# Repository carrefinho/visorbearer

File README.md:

# Visorbearer

Visorbearer is a 32-key unibody split wireless keyboard featuring 8 RGB LED indicators.

Named after [hummingbirds in the genus Augastes](https://en.wikipedia.org/wiki/Visorbearer) for the Hummingbird layout connection and distinctive white bands on their chests that resemble the LED indicators.

> [!WARNING]
> This is a work in progress.

## To-Do

- [ ] Build Guide & BOM
- [ ] Case Printing Guide
- [ ] Alternative layout case files and guide
- [x] Revision 2 PCB testing + power profiling
- [x] Firmware Notes
- [ ] Design write-up
- [ ] More photos

## Design

https://github.com/user-attachments/assets/812049e3-29ce-48d4-8fe3-20bf21285e64

- 2x 4-segment RGB LED indicators
   - Discreet dead-front design: completely invisible when off
   - Connection bar: Bluetooth profiles and modifier keys
   - Battery bar: percentage and charging status
   - Powered by two TI LP5012 drivers with automatic low-power mode
- 32-key Hummingbird-ish layout with splay and inverted thumb cluster
   - Down to 26-key with case and plate variants
      - 2U thumb key support
- Hot-swap Kailh Choc v1 switches in Choc (18x17mm) spacing
   - <details> <summary>Limited Choc v2 compatibility</summary>

      The PCB is incompatible with older Choc v2 switches that have a third stabilizing pin. Newer Choc v2 releases without this pin work fine, such as: Lofree POM Phantom/Ghost/Specter/Hades and Kailh Hide Mountain/White Rain/Deep Sea Mini Islet/Deep Sea Mini Whale.

      Note that, for Choc v2, there are very few off-the-shelf options for choc-spaced keycaps with MX stems: as of late 2025, the only two are [Taihao THCS](https://shop.tai-hao.com/categories/thcs-low-profile-keycaps) and [Asymplex MX-stem Chicago Steno](https://www.asymplex.xyz/product/made-to-order-mx-stem-cs-kits). You could also 3D-print your own keycaps.

   </details>
- Seeed Studio XIAO nRF52840 **Plus** controller on ZMK firmware
- 3D-printed case and switch plate with switch puller grooves
   - Easily accessible reset button

<picture>
  <source media="(prefers-color-scheme: dark)" srcset="./docs/images/visorbearer-dimensions-dark.png">
  <source media="(prefers-color-scheme: light)" srcset="./docs/images/visorbearer-dimensions-light.png">
  
</picture>

## Build Guide

> [!NOTE]
> Revision 2 PCB is tested and working. Build guide is work in progress.

[View the PCB on KiCanvas.](https://kicanvas.org/?github=https%3A%2F%2Fgithub.com%2Fcarrefinho%2Fvisorbearer%2Ftree%2Fmain%2Fvisorbearer-pcb)

[Find the build guide here.](/docs/build-guide.md)

## Firmware

[Find the ZMK module here.](https://github.com/carrefinho/visorbearer-zmk-module)

## Gallery

## Inspirations & Acknowledgments

- Aesthetics
   - [GEIGEIGEIST/TOTEM](https://github.com/GEIGEIGEIST/TOTEM)
   - [weteor/Grumpy](https://github.com/weteor/Grumpy)
   - [dohn-joh/alias](https://github.com/dohn-joh/alias)
- Layout
   - [bennytrouser/NostrumX](https://github.com/bennytrouser/NostrumX)
   - [davidphilipbarr/hypergolic](https://github.com/davidphilipbarr/hypergolic)
   - [davidphilipbarr/paroxysm](https://github.com/davidphilipbarr/paroxysm)
   - [grassfedreeve/akohekohe](https://github.com/grassfedreeve/akohekohe)
   - [hazels-garage/bad-wings](https://github.com/hazels-garage/bad-wings/tree/master/v2)
   - [kilipan/zilpzalp](https://github.com/kilipan/zilpzalp)
   - [weteor/Fitis](https://github.com/weteor/Fitis)
   - [weteor/Tipper-TF](https://github.com/weteor/Tipper-TF)
- LED indicator
   - [GEIGEIGEIST/KLOTZ](https://github.com/GEIGEIGEIST/KLOTZ)
   - [caksoylar/zmk-rgbled-widget](https://github.com/caksoylar/zmk-rgbled-widget): LED code
- Case
   - [duckyb/urchin](https://github.com/duckyb/urchin): Snap fit design
- And the lovely folks on the Fingerpunch discord who were along for the ride!

## License

Visorbearer is licensed under CERN-OHL-P-2.0.

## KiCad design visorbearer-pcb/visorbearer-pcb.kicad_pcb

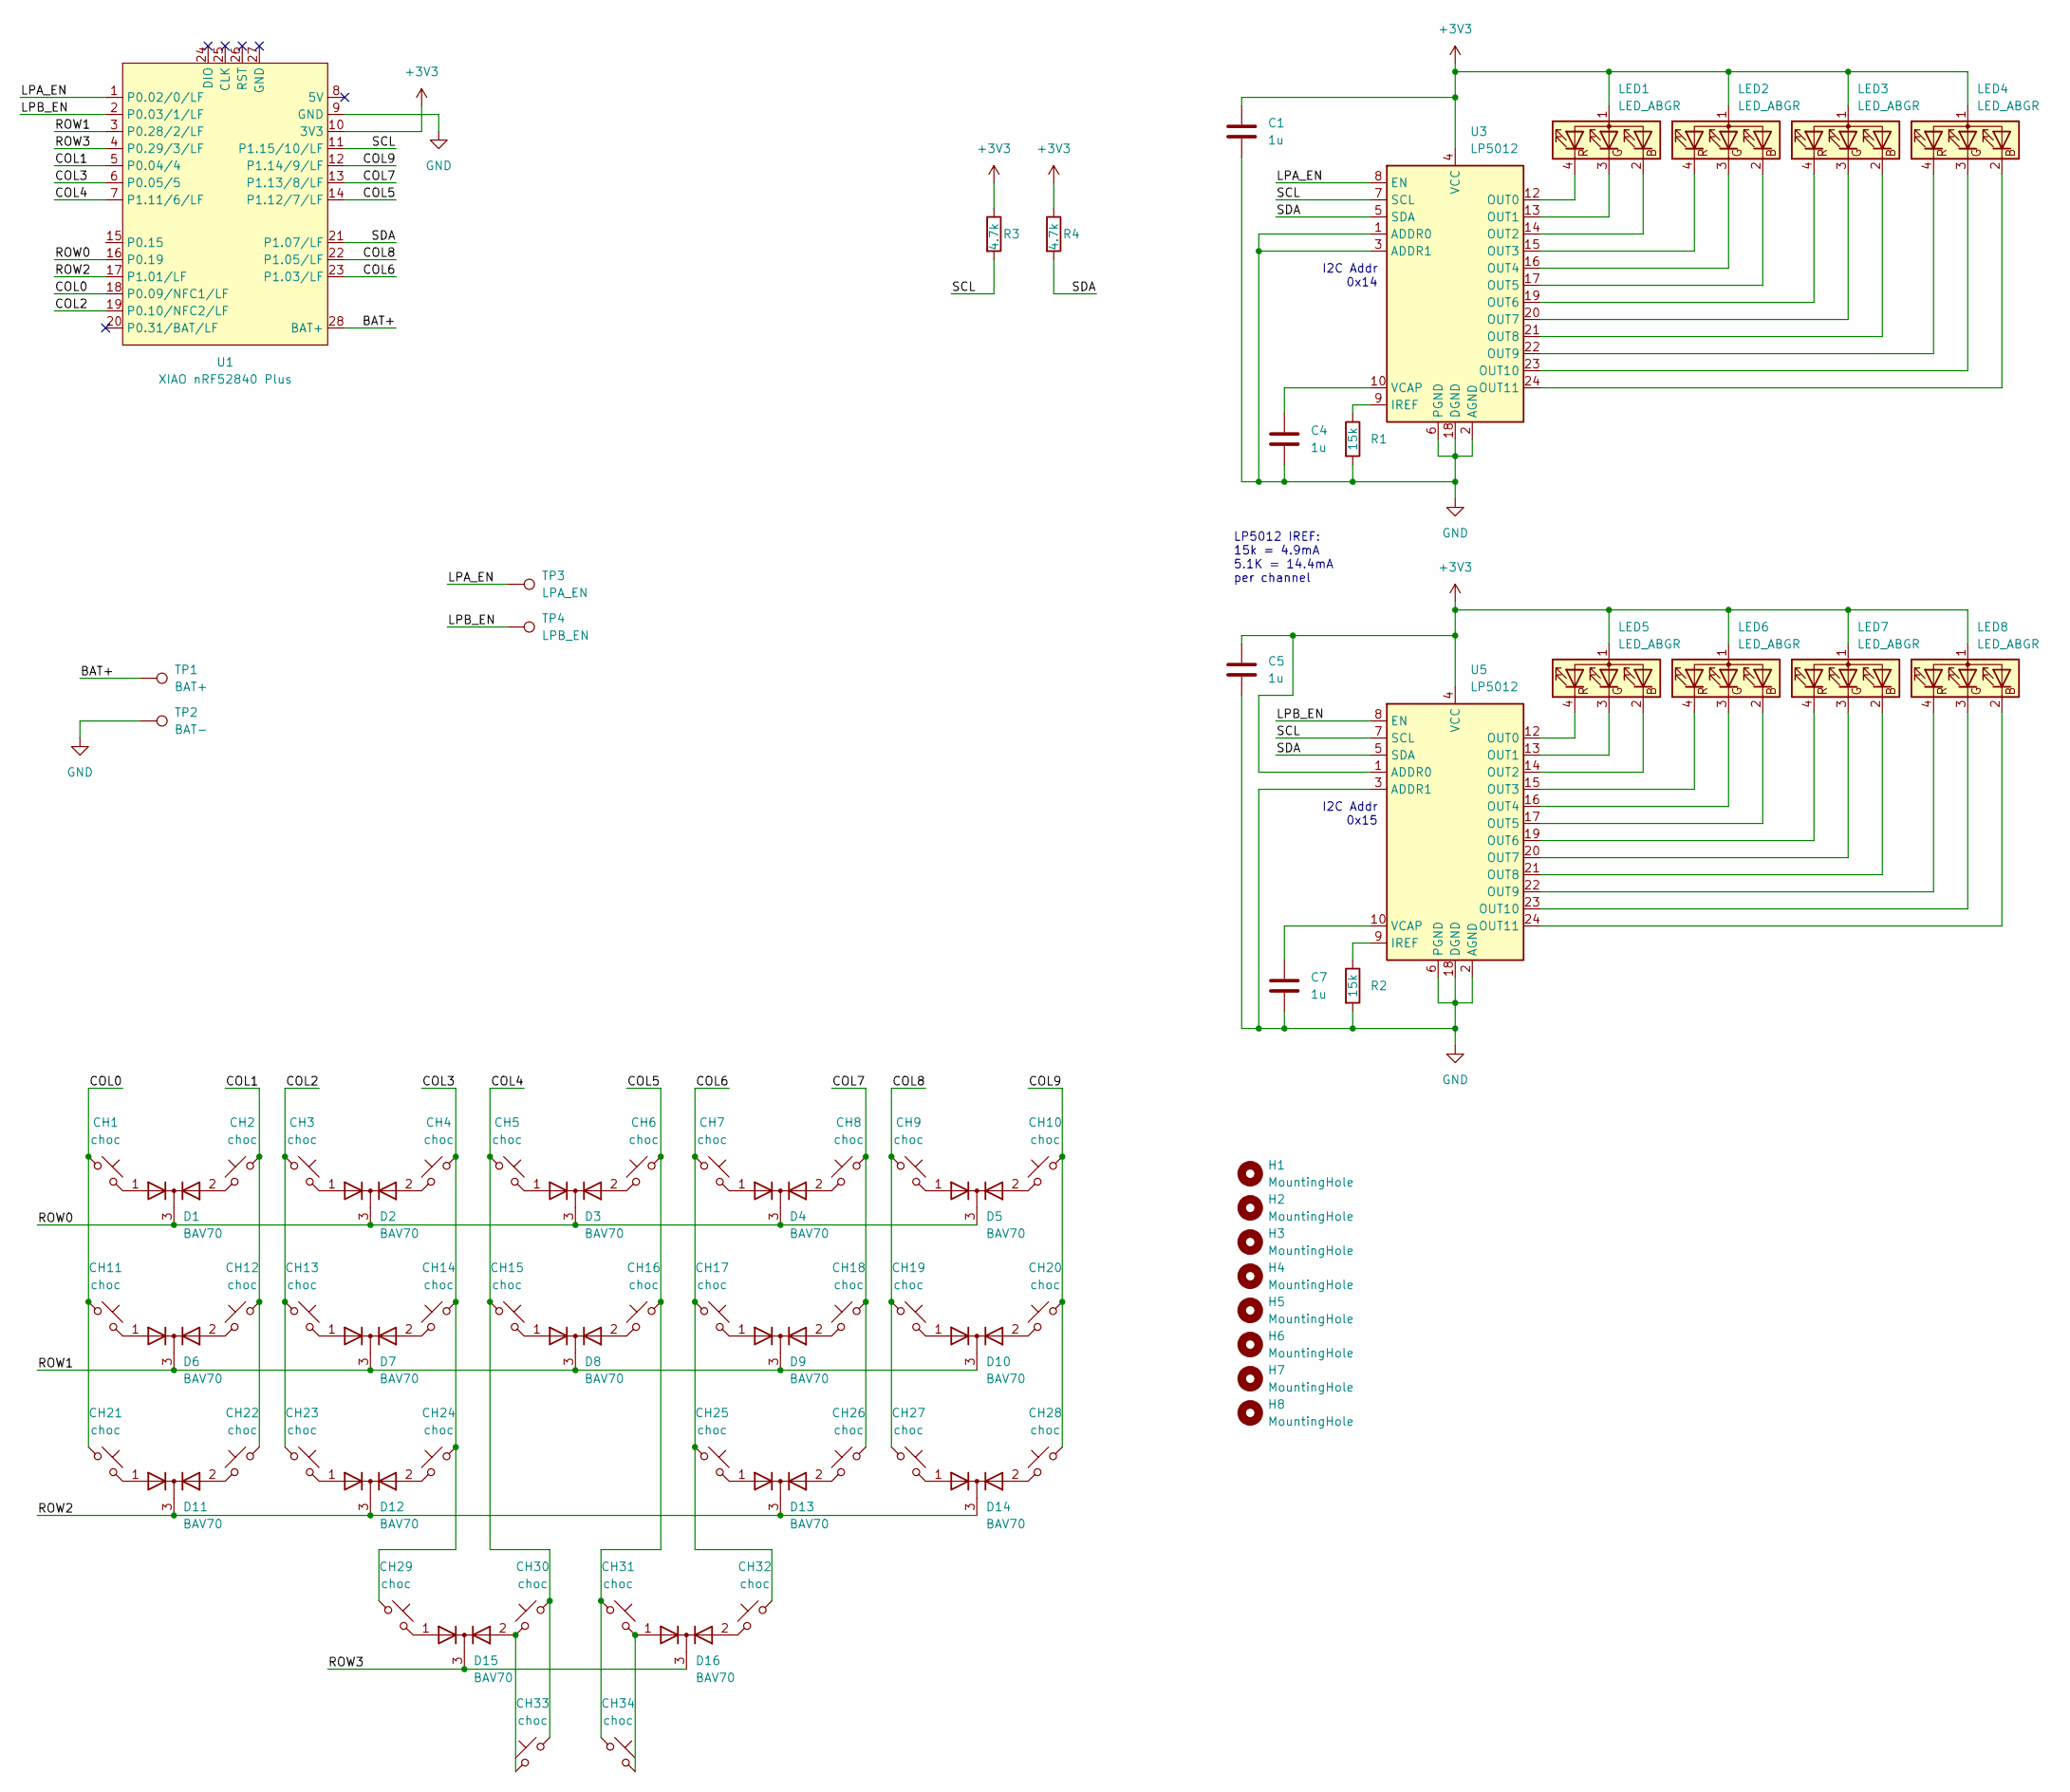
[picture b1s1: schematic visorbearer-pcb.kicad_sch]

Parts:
C1, C4, C5, C7: 1u; C_0603_1608Metric
CH1, CH2, CH3, CH4, CH5, CH6, CH7, CH8, CH9, CH10, CH11, CH12, CH13, CH14, CH15, CH16, CH17, CH18, CH19, CH20, CH21, CH22, CH23, CH24, CH25, CH26, CH27, CH28, CH29, CH30, CH31, CH32, CH33, CH34: choc; SW_choc_v1v2_noStab_HS_MBK_1u
D1, D2, D3, D4, D5, D6, D7, D8, D9, D10, D11, D12, D13, D14, D15, D16: BAV70; SOT-23_Handsoldering
H1, H2, H3, H4, H5, H6, H7, H8: MountingHole; MountingHole_2.2mm_M2_ISO7380_Pad_TopBottom_BackSilkRing
LED1, LED2, LED3, LED4, LED5, LED6, LED7, LED8: LED_ABGR; LED_Cree-PLCC4_2x2mm_CW
R1, R2: 15k; R_0603_1608Metric
R3, R4: 4.7k; R_0603_1608Metric
TP1: BAT+; TestPoint_Pad_3.0x3.0mm
TP2: BAT-; TestPoint_Pad_3.0x3.0mm
TP3: LPA_EN; TestPoint_Pad_D1.5mm
TP4: LPB_EN; TestPoint_Pad_D1.5mm
U1: XIAO nRF52840 Plus; Xiao_nRF52840_Plus
U3, U5: LP5012; TSSOP-24_4.4x7.8mm_P0.65mm

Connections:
+3V3: C1.1, C5.1, LED1.1 (A), LED2.1 (A), LED3.1 (A), LED4.1 (A), LED5.1 (A), LED6.1 (A), LED7.1 (A), LED8.1 (A), R3.1, R4.1, U1.10 (3V3), U3.4 (VCC), U5.1 (ADDR0), U5.4 (VCC)
/BAT+: TP1.1, U1.28 (BAT+)
/COL0: CH1.1, CH11.1, CH21.1, U1.18 (P0.09/NFC1/LF)
/COL1: CH2.1, CH12.1, CH22.1, U1.5 (P0.04/4)
/COL2: CH3.1, CH13.1, CH23.1, U1.19 (P0.10/NFC2/LF)
/COL3: CH4.1, CH14.1, CH24.1, CH29.1, U1.6 (P0.05/5)
/COL4: CH5.1, CH15.1, CH30.1, CH33.1, U1.7 (P1.11/6/LF)
/COL5: CH6.1, CH16.1, CH31.1, CH34.1, U1.14 (P1.12/7/LF)
/COL6: CH7.1, CH17.1, CH25.1, CH32.1, U1.23 (P1.03/LF)
/COL7: CH8.1, CH18.1, CH26.1, U1.13 (P1.13/8/LF)
/COL8: CH9.1, CH19.1, CH27.1, U1.22 (P1.05/LF)
/COL9: CH10.1, CH20.1, CH28.1, U1.12 (P1.14/9/LF)
/LPA_EN: TP3.1, U1.1 (P0.02/0/LF), U3.8 (EN)
/LPB_EN: TP4.1, U1.2 (P0.03/1/LF), U5.8 (EN)
/ROW0: D1.3 (K), D2.3 (K), D3.3 (K), D4.3 (K), D5.3 (K), U1.16 (P0.19)
/ROW1: D6.3 (K), D7.3 (K), D8.3 (K), D9.3 (K), D10.3 (K), U1.3 (P0.28/2/LF)
/ROW2: D11.3 (K), D12.3 (K), D13.3 (K), D14.3 (K), U1.17 (P1.01/LF)
/ROW3: D15.3 (K), D16.3 (K), U1.4 (P0.29/3/LF)
/SCL: R3.2, U1.11 (P1.15/10/LF), U3.7 (SCL), U5.7 (SCL)
/SDA: R4.2, U1.21 (P1.07/LF), U3.5 (SDA), U5.5 (SDA)
GND: C1.2, C4.2, C5.2, C7.2, R1.2, R2.2, TP2.1, U1.9 (GND), U3.1 (ADDR0), U3.2 (AGND), U3.3 (ADDR1), U3.6 (PGND), U3.18 (DGND), U5.2 (AGND), U5.3 (ADDR1), U5.6 (PGND), U5.18 (DGND)
unnamed: CH1.2, D1.1 (A)
unnamed: CH2.2, D1.2 (A)
unnamed: CH3.2, D2.1 (A)
unnamed: CH4.2, D2.2 (A)
unnamed: CH5.2, D3.1 (A)
unnamed: CH6.2, D3.2 (A)
unnamed: CH7.2, D4.1 (A)
unnamed: CH8.2, D4.2 (A)
unnamed: CH9.2, D5.1 (A)
unnamed: CH10.2, D5.2 (A)
unnamed: CH11.2, D6.1 (A)
unnamed: CH12.2, D6.2 (A)
unnamed: CH13.2, D7.1 (A)
unnamed: CH14.2, D7.2 (A)
unnamed: CH15.2, D8.1 (A)
unnamed: CH16.2, D8.2 (A)
unnamed: CH17.2, D9.1 (A)
unnamed: CH18.2, D9.2 (A)
unnamed: CH19.2, D10.1 (A)
unnamed: CH20.2, D10.2 (A)
unnamed: CH21.2, D11.1 (A)
unnamed: CH22.2, D11.2 (A)
unnamed: CH23.2, D12.1 (A)
unnamed: CH24.2, D12.2 (A)
unnamed: CH25.2, D13.1 (A)
unnamed: CH26.2, D13.2 (A)
unnamed: CH27.2, D14.1 (A)
unnamed: CH28.2, D14.2 (A)
unnamed: CH29.2, D15.1 (A)
unnamed: CH30.2, CH33.2, D15.2 (A)
unnamed: CH31.2, CH34.2, D16.1 (A)
unnamed: CH32.2, D16.2 (A)
unnamed: LED1.2 (BK), U3.14 (OUT2)
unnamed: LED1.3 (GK), U3.13 (OUT1)
unnamed: LED1.4 (RK), U3.12 (OUT0)
unnamed: LED2.2 (BK), U3.17 (OUT5)
unnamed: LED2.3 (GK), U3.16 (OUT4)
unnamed: LED2.4 (RK), U3.15 (OUT3)
unnamed: LED3.2 (BK), U3.21 (OUT8)
unnamed: LED3.3 (GK), U3.20 (OUT7)
unnamed: LED3.4 (RK), U3.19 (OUT6)
unnamed: LED4.2 (BK), U3.24 (OUT11)
unnamed: LED4.3 (GK), U3.23 (OUT10)
unnamed: LED4.4 (RK), U3.22 (OUT9)
unnamed: LED5.2 (BK), U5.14 (OUT2)
unnamed: LED5.3 (GK), U5.13 (OUT1)
unnamed: LED5.4 (RK), U5.12 (OUT0)
unnamed: LED6.2 (BK), U5.17 (OUT5)
unnamed: LED6.3 (GK), U5.16 (OUT4)
unnamed: LED6.4 (RK), U5.15 (OUT3)
unnamed: LED7.2 (BK), U5.21 (OUT8)
unnamed: LED7.3 (GK), U5.20 (OUT7)
unnamed: LED7.4 (RK), U5.19 (OUT6)
unnamed: LED8.2 (BK), U5.24 (OUT11)
unnamed: LED8.3 (GK), U5.23 (OUT10)
unnamed: LED8.4 (RK), U5.22 (OUT9)
unnamed: R1.1, U3.9 (IREF)
unnamed: C4.1, U3.10 (VCAP)
unnamed: R2.1, U5.9 (IREF)
unnamed: C7.1, U5.10 (VCAP)

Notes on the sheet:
LP5012 IREF: 15k = 4.9mA 5.1K = 14.4mA per channel
I2C Addr 0x14
I2C Addr 0x15

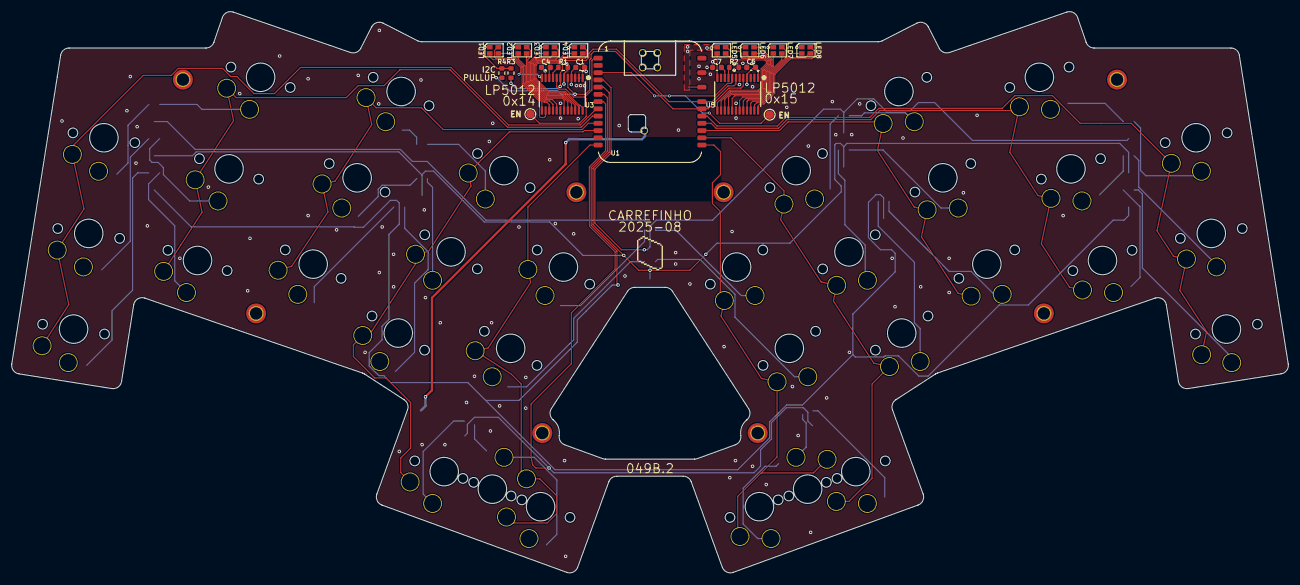
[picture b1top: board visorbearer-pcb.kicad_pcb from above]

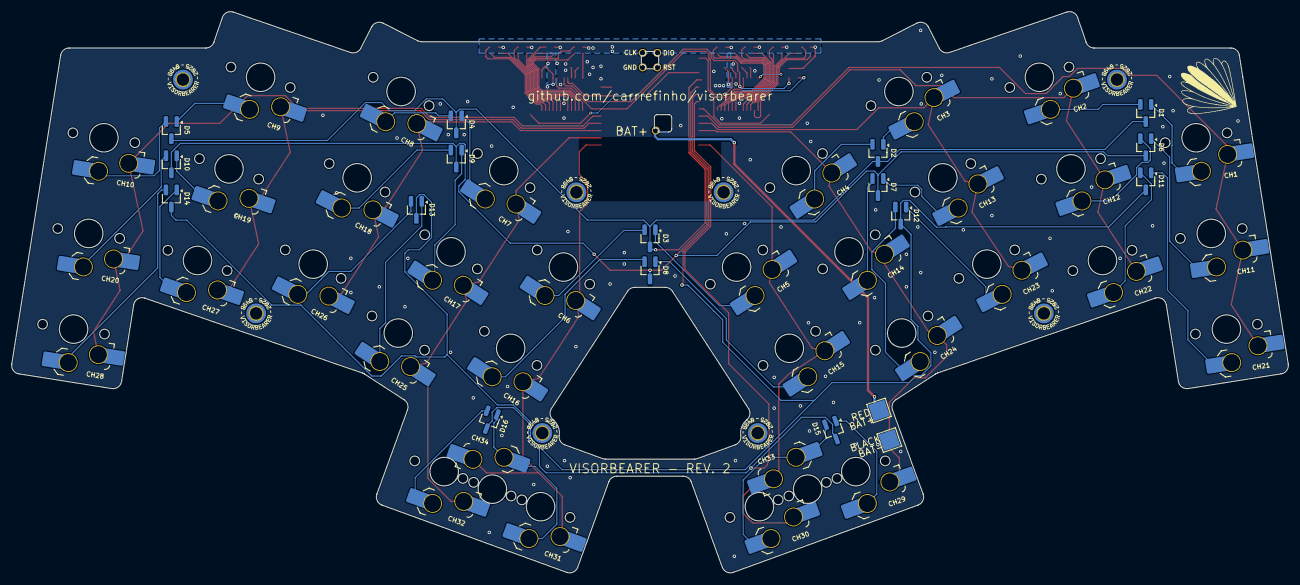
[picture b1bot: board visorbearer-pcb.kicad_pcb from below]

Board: 2 copper layers, 224.0 x 98.5 mm, 81 parts (52 on the bottom side), 81 nets.

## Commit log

2025-08-12 fix image links
2025-08-12 default to light?
2025-08-12 rename image files to remove spaces
2025-08-12 update image
2025-08-13 new dimension images
2025-08-13 lil lighter light mode
2025-08-13 more v2 caveat
2025-08-13 wording
2025-08-13 acknowlegments and caveat wording
2025-08-13 update renders
2025-08-13 consistent lower case v
2025-08-13 reword footnote
2025-08-13 reword footnote 2
2025-08-14 add rev 2 pcb warning
2025-08-14 move choc v2 support caveat to collapsed block
2025-08-14 remove bold inside collapsed block
2025-08-15 heading image init
2025-08-15 add hero image
2025-08-15 alleged markdown solution for adaptive appearance
2025-08-15 Revert "alleged markdown solution for adaptive appearance"
    This reverts commit 2164302b4b408629c76edc546fdcd8051a92ab56.
2025-08-15 messing with image links
2025-08-15 update readme and add loicense
2025-08-16 update readme and heading image
2025-08-16 adjust heading image
2025-08-16 shrink header a bit
2025-08-16 add video
2025-08-16 Add PCB
2025-08-19 pcb: change to hand-solderable diode footprint, move battery pads, add LP5012 EN test points
2025-08-20 add standard case files & update pcb
2025-08-20 use real photo as hero image
2025-08-20 add rounded corner to hero image
2025-08-20 update heading
2025-08-20 update video
2025-08-20 add gallery
2025-08-20 correct some typos
2025-09-21 add ergogen files
2025-10-12 update readme and work on case printing guide
2025-10-16 update docs
2025-10-16 update pcb assembly guide
2025-10-16 increase text size of LED component orientation image
2025-10-16 update LED component orientation image
2025-10-16 add links in build guide
2025-10-20 update case priting guide
2025-10-20 update BOM, fix broken links
2025-10-22 update heading images
2025-10-22 new hero image
2025-10-22 update hero image
2025-10-28 update readme & docs
2025-12-13 add assembly diagrams
2025-12-13 update choc v2 keycap info in the readme
